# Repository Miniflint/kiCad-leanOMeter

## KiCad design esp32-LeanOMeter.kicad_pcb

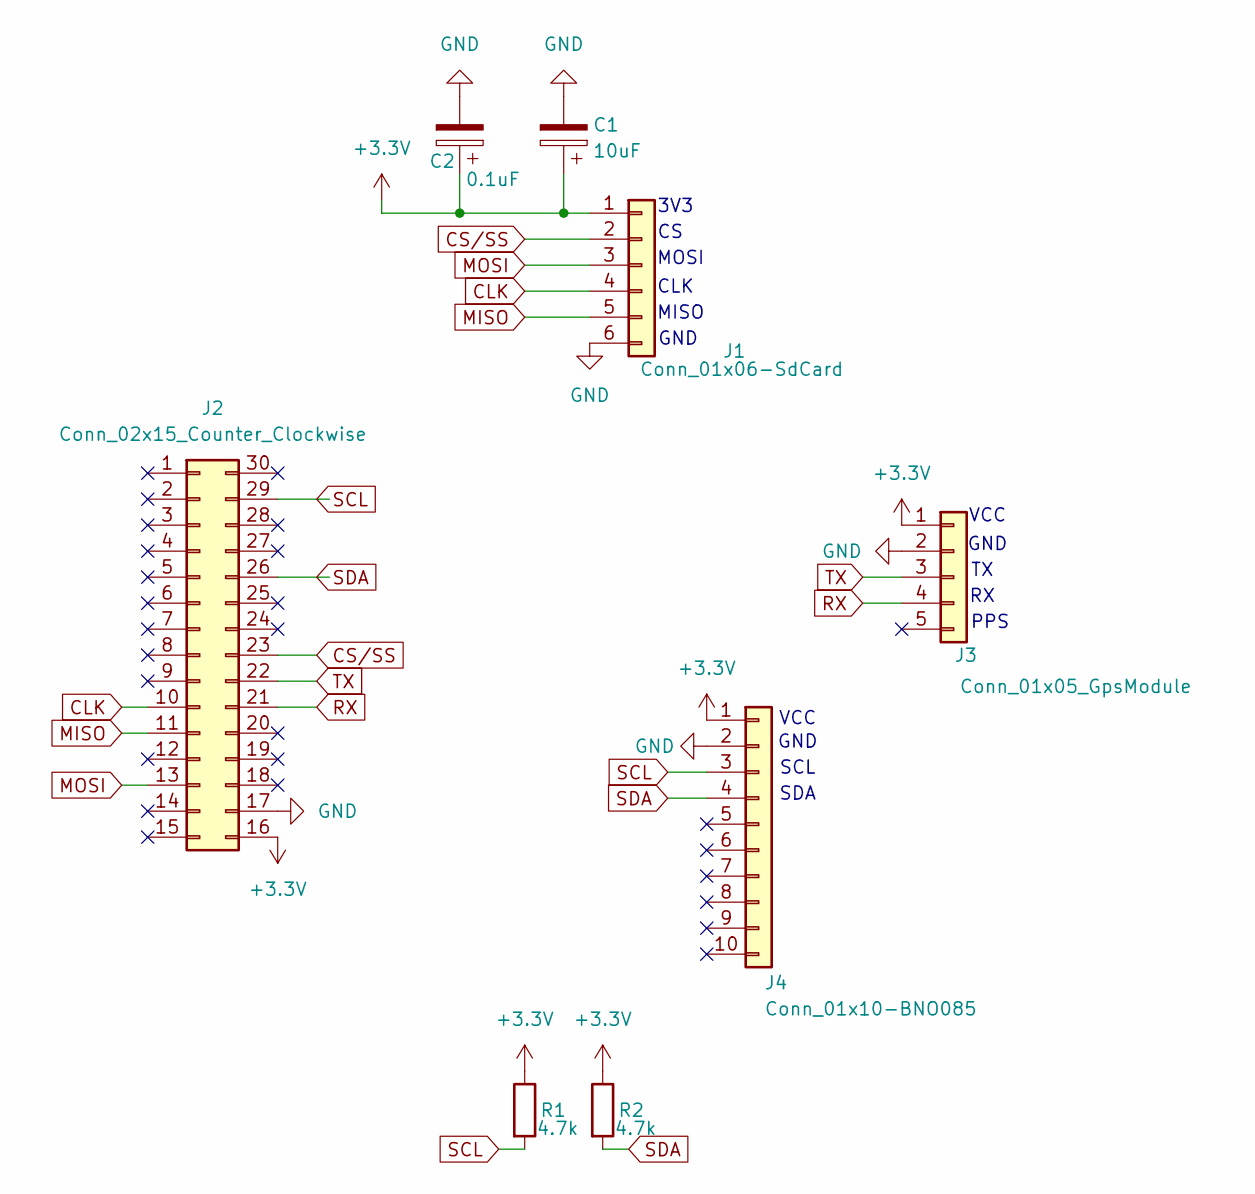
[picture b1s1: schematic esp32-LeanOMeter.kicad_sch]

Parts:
C1: 10uF; CP_Radial_D5.0mm_P2.00mm
C2: 0.1uF; CP_Radial_D4.0mm_P1.50mm
J1: Conn_01x06-SdCard; PinHeader_1x06_P2.54mm_Vertical
J2: Conn_02x15_Counter_Clockwise; ESP32-C3-DevKitM-1
J3: Conn_01x05_GpsModule; PinHeader_1x05_P2.54mm_Vertical
J4: Conn_01x10-BNO085; PinHeader_1x10_P2.54mm_Vertical
R1, R2: 4.7k; R_Axial_DIN0207_L6.3mm_D2.5mm_P7.62mm_Horizontal

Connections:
+3.3V: C1.1, C2.1, J1.1, J2.16, J3.1, J4.1, R1.1, R2.1
CLK: J1.4, J2.10
CS/SS: J1.2, J2.23
GND: C1.2, C2.2, J1.6, J2.17, J3.2, J4.2
MISO: J1.5, J2.11
MOSI: J1.3, J2.13
RX: J2.21, J3.4
SCL: J2.29, J4.3, R1.2
SDA: J2.26, J4.4, R2.2
TX: J2.22, J3.3

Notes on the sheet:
PPS
MOSI
SDA
GND
3V3
SCL
MISO
VCC
GND
CLK

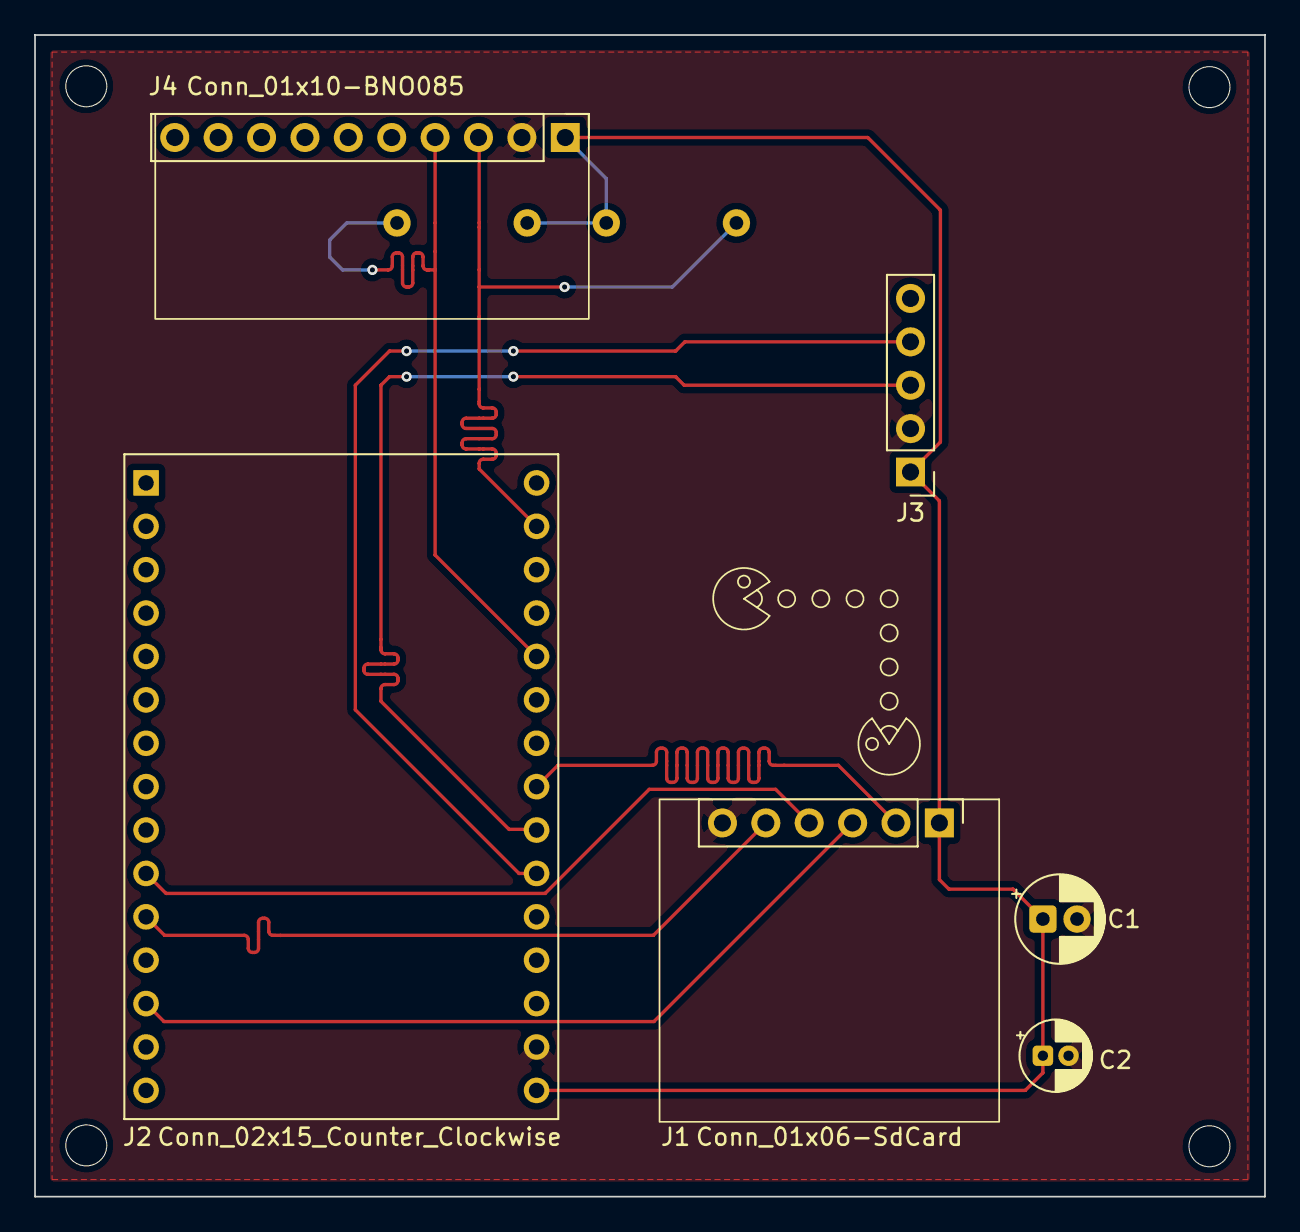
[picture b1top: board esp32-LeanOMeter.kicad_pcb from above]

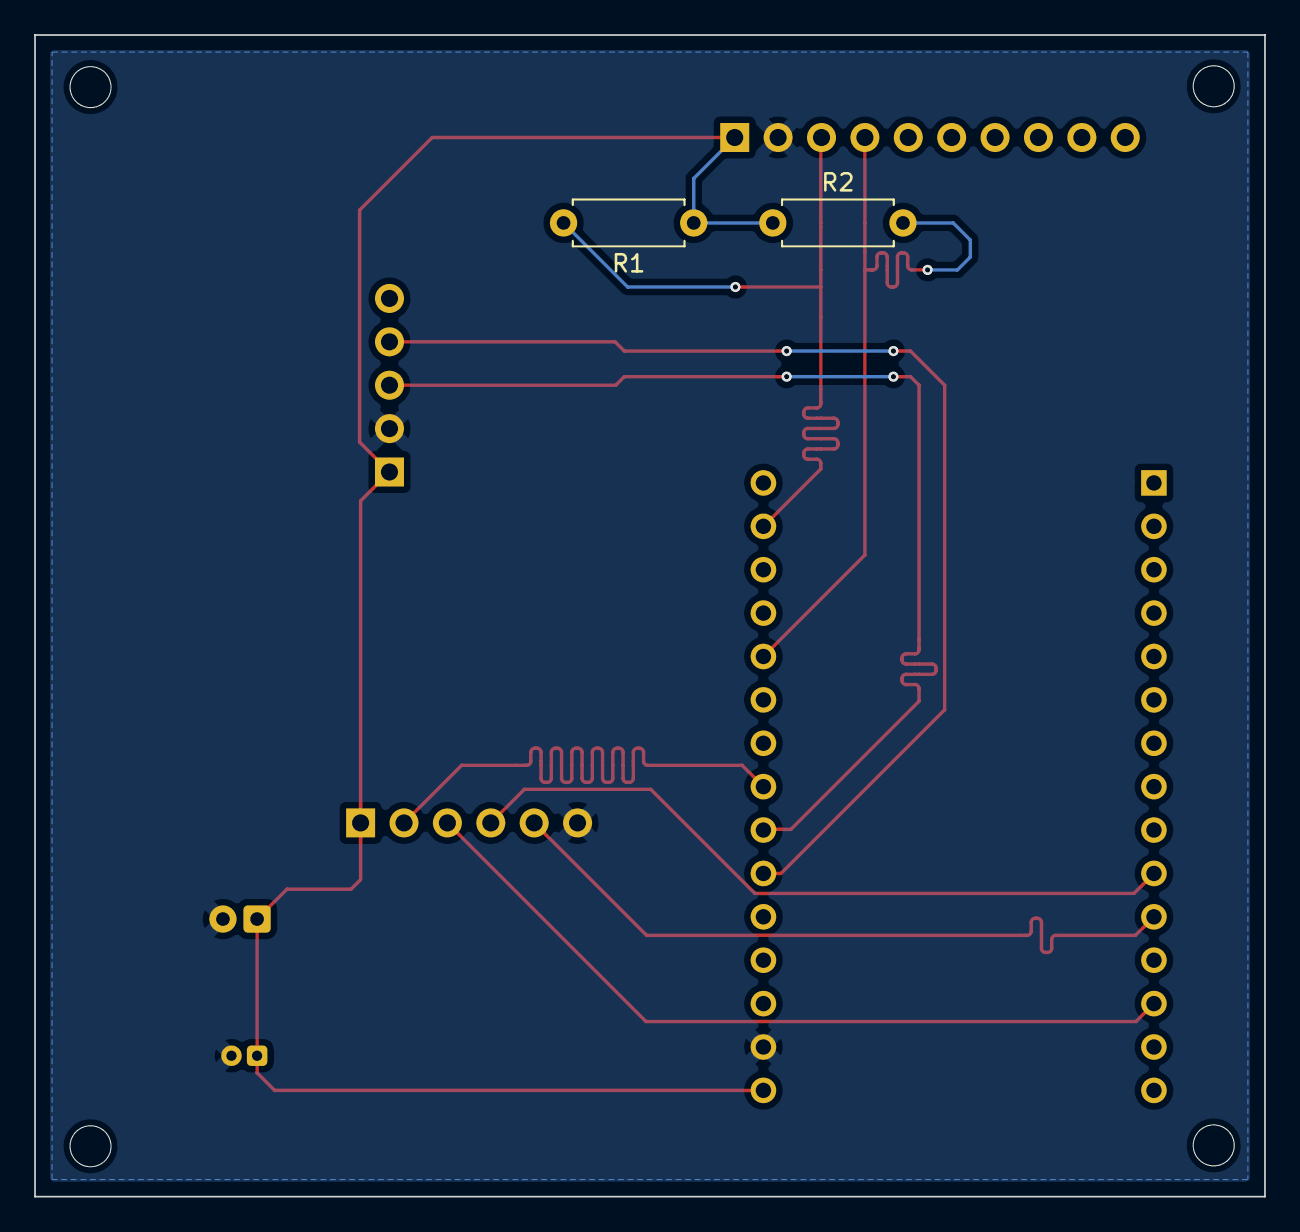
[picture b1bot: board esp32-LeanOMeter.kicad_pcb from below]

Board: 2 copper layers, 72.0 x 68.0 mm, 8 parts (2 on the bottom side), 10 nets.

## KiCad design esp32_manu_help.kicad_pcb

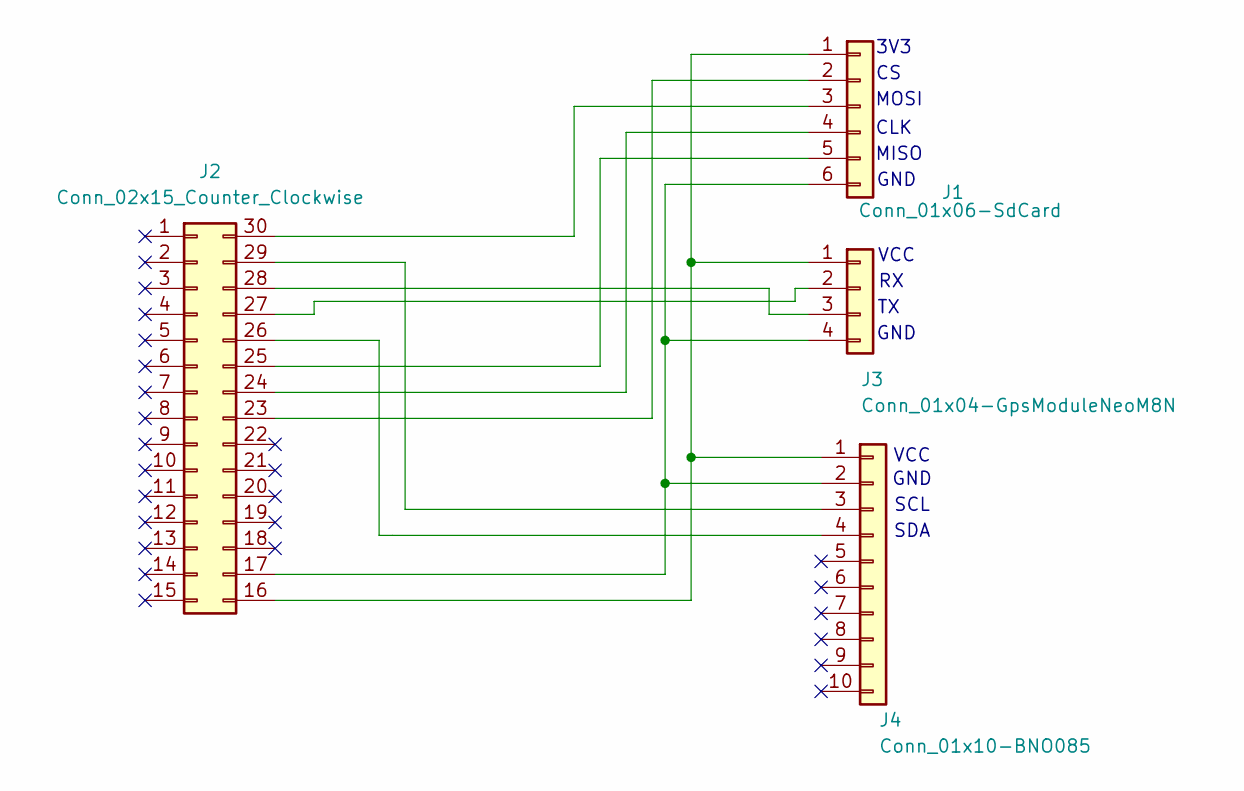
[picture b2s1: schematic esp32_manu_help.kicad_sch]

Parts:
J1: Conn_01x06-SdCard; PinHeader_1x06_P2.54mm_Vertical
J2: Conn_02x15_Counter_Clockwise; ESP32-C3-DevKitM-1
J3: Conn_01x04-GpsModuleNeoM8N; PinHeader_1x04_P2.54mm_Vertical
J4: Conn_01x10-BNO085; PinHeader_1x10_P2.54mm_Vertical

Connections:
unnamed: J1.1, J2.16, J3.1, J4.1
unnamed: J1.2, J2.23
unnamed: J1.3, J2.30
unnamed: J1.4, J2.24
unnamed: J1.5, J2.25
unnamed: J1.6, J2.17, J3.4, J4.2
unnamed: J2.26, J4.4
unnamed: J2.27, J3.2
unnamed: J2.28, J3.3
unnamed: J2.29, J4.3

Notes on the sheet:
MOSI
SDA
GND
3V3
SCL
MISO
VCC
GND
CLK

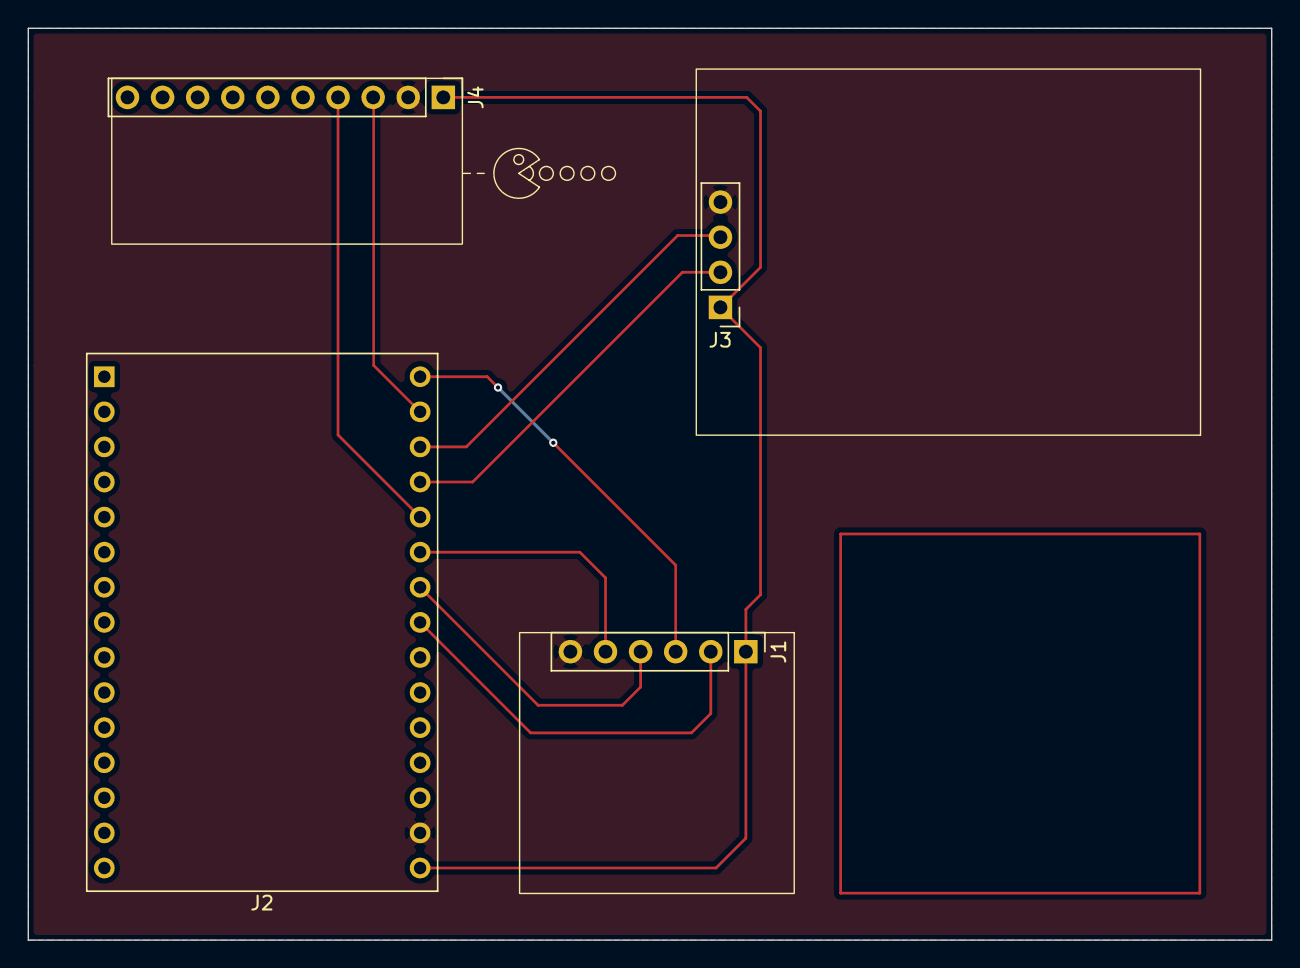
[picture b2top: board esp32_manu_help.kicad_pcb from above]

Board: 2 copper layers, 90.0 x 66.0 mm, 4 parts (0 on the bottom side), 10 nets.
